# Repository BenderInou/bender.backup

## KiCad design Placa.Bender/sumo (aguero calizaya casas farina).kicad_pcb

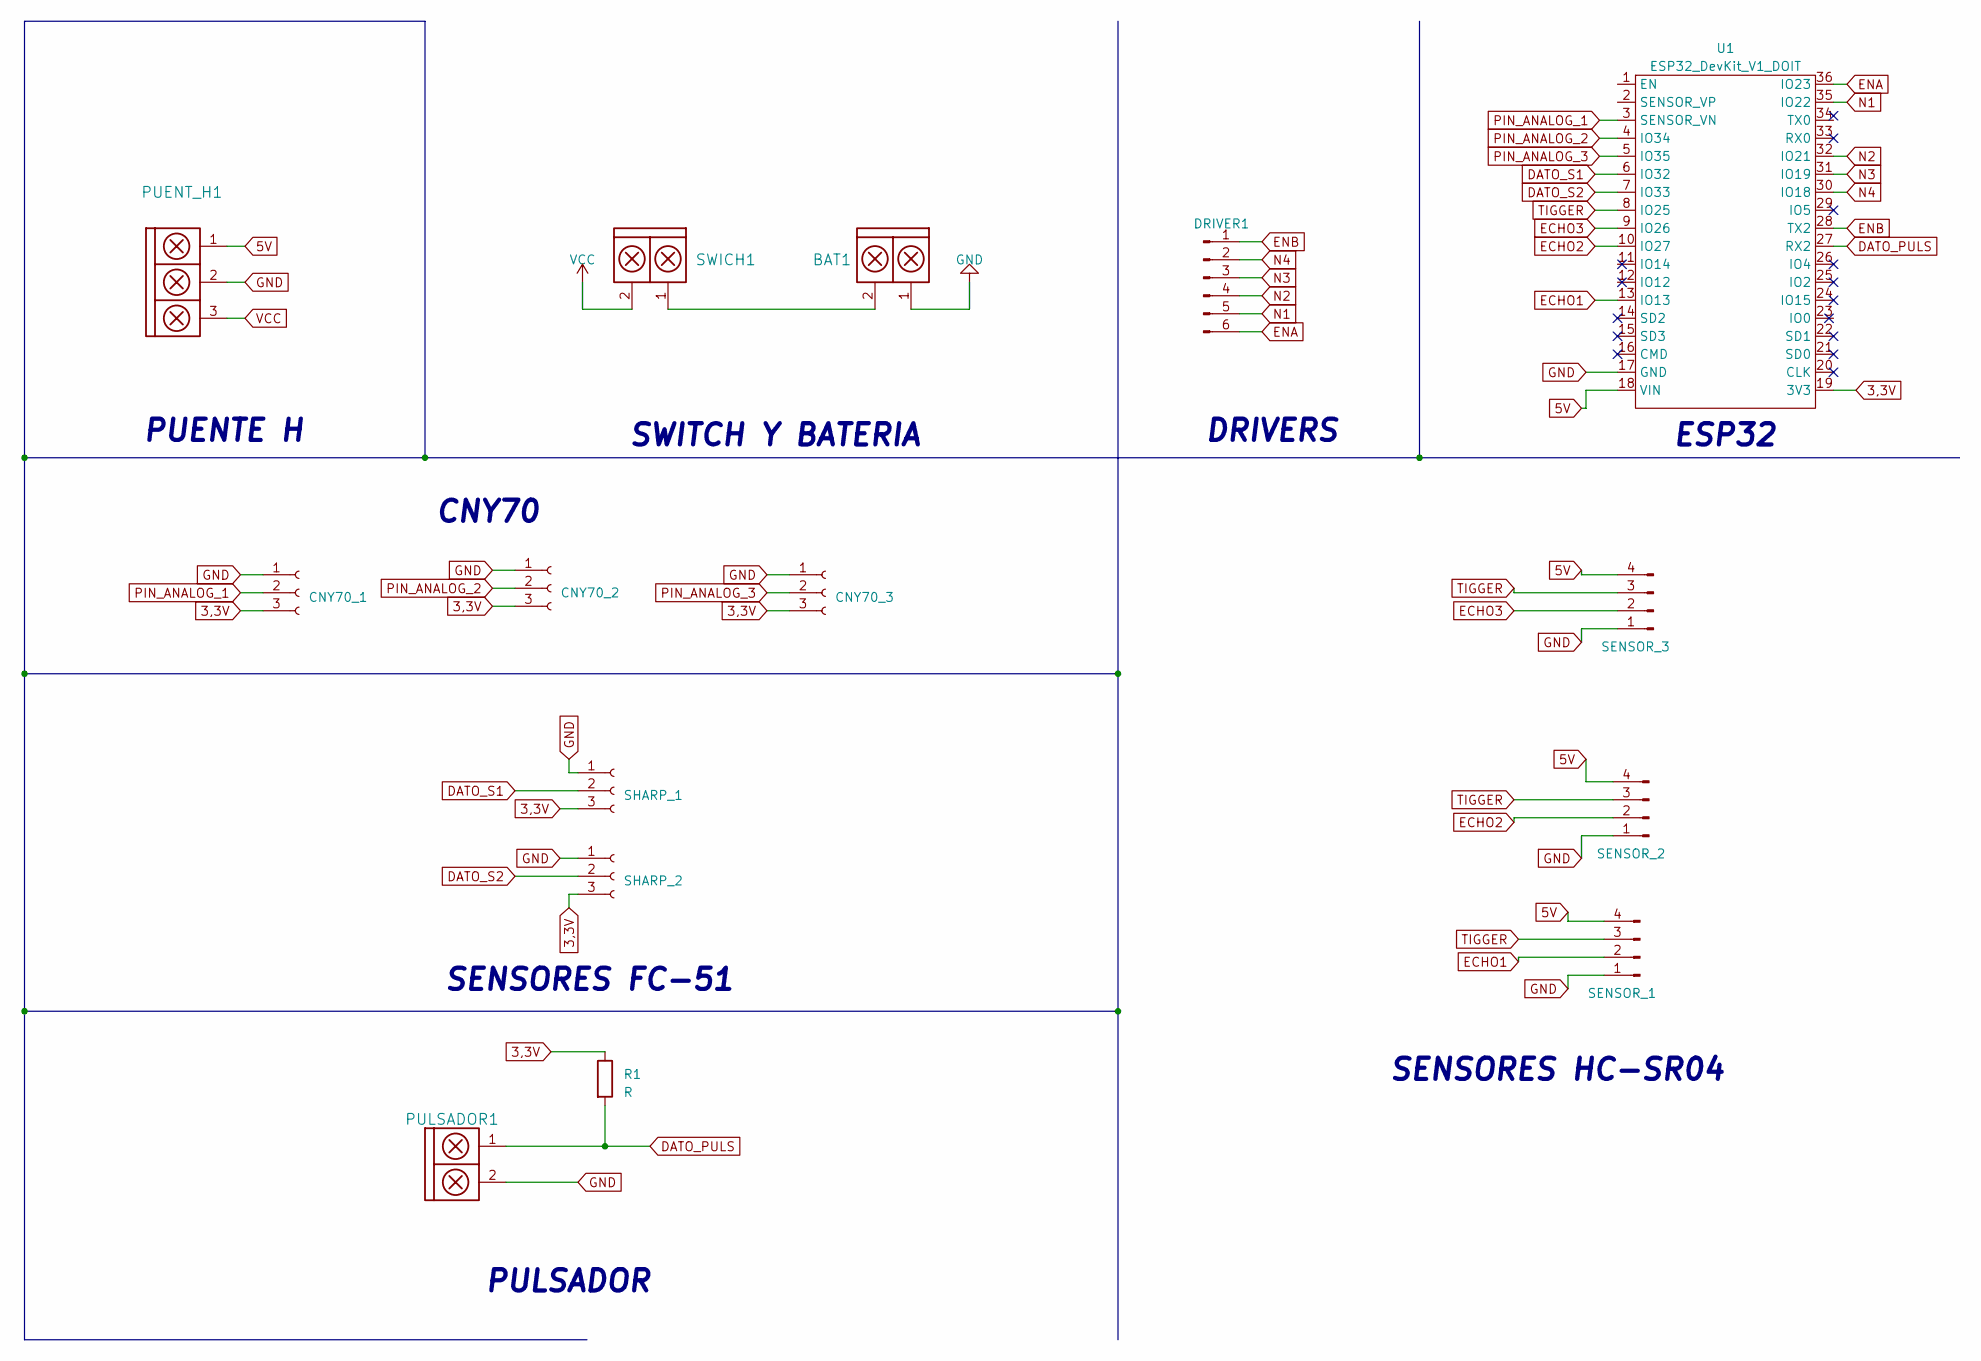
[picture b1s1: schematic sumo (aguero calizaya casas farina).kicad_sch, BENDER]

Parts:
BAT1: BORNERA2
CNY70_1, CNY70_2, CNY70_3: Pin_Header_3
DRIVER1: Pin_Header_6
PUENT_H1: \; BORNERA3
PULSADOR1: BORNERA2
R1: R; RES0.2
SENSOR_1, SENSOR_2, SENSOR_3: Pin_Header_Angled_1x04
SHARP_1, SHARP_2: Pin_Header_3
SWICH1: BORNERA2
U1: ESP32_DevKit_V1_DOIT; ESP32_DEVKIT_V1_DOIT

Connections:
3,3V: CNY70_1.3, CNY70_2.3, CNY70_3.3, R1.1, SHARP_1.3, SHARP_2.3, U1.19 (3V3)
5V: PUENT_H1.1, SENSOR_1.4, SENSOR_2.4, SENSOR_3.4, U1.18 (VIN)
DATO_PULS: PULSADOR1.1, R1.2, U1.27 (RX2)
DATO_S1: SHARP_1.2, U1.6 (IO32)
DATO_S2: SHARP_2.2, U1.7 (IO33)
ECHO1: SENSOR_1.2, U1.13 (IO13)
ECHO2: SENSOR_2.2, U1.10 (IO27)
ECHO3: SENSOR_3.2, U1.9 (IO26)
ENA: DRIVER1.6, U1.36 (IO23)
ENB: DRIVER1.1, U1.28 (TX2)
GND: BAT1.1, CNY70_1.1, CNY70_2.1, CNY70_3.1, PUENT_H1.2, PULSADOR1.2, SENSOR_1.1, SENSOR_2.1, SENSOR_3.1, SHARP_1.1, SHARP_2.1, U1.17 (GND)
N1: DRIVER1.5, U1.35 (IO22)
N2: DRIVER1.4, U1.32 (IO21)
N3: DRIVER1.3, U1.31 (IO19)
N4: DRIVER1.2, U1.30 (IO18)
unnamed: BAT1.2, SWICH1.1
PIN_ANALOG_1: CNY70_1.2, U1.3 (SENSOR_VN)
PIN_ANALOG_2: CNY70_2.2, U1.4 (IO34)
PIN_ANALOG_3: CNY70_3.2, U1.5 (IO35)
TIGGER: SENSOR_1.3, SENSOR_2.3, SENSOR_3.3, U1.8 (IO25)
VCC: PUENT_H1.3, SWICH1.2

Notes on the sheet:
SENSORES FC-51
PUENTE H
PULSADOR
CNY70
DRIVERS
SWITCH Y BATERIA
SENSORES HC-SR04
ESP32

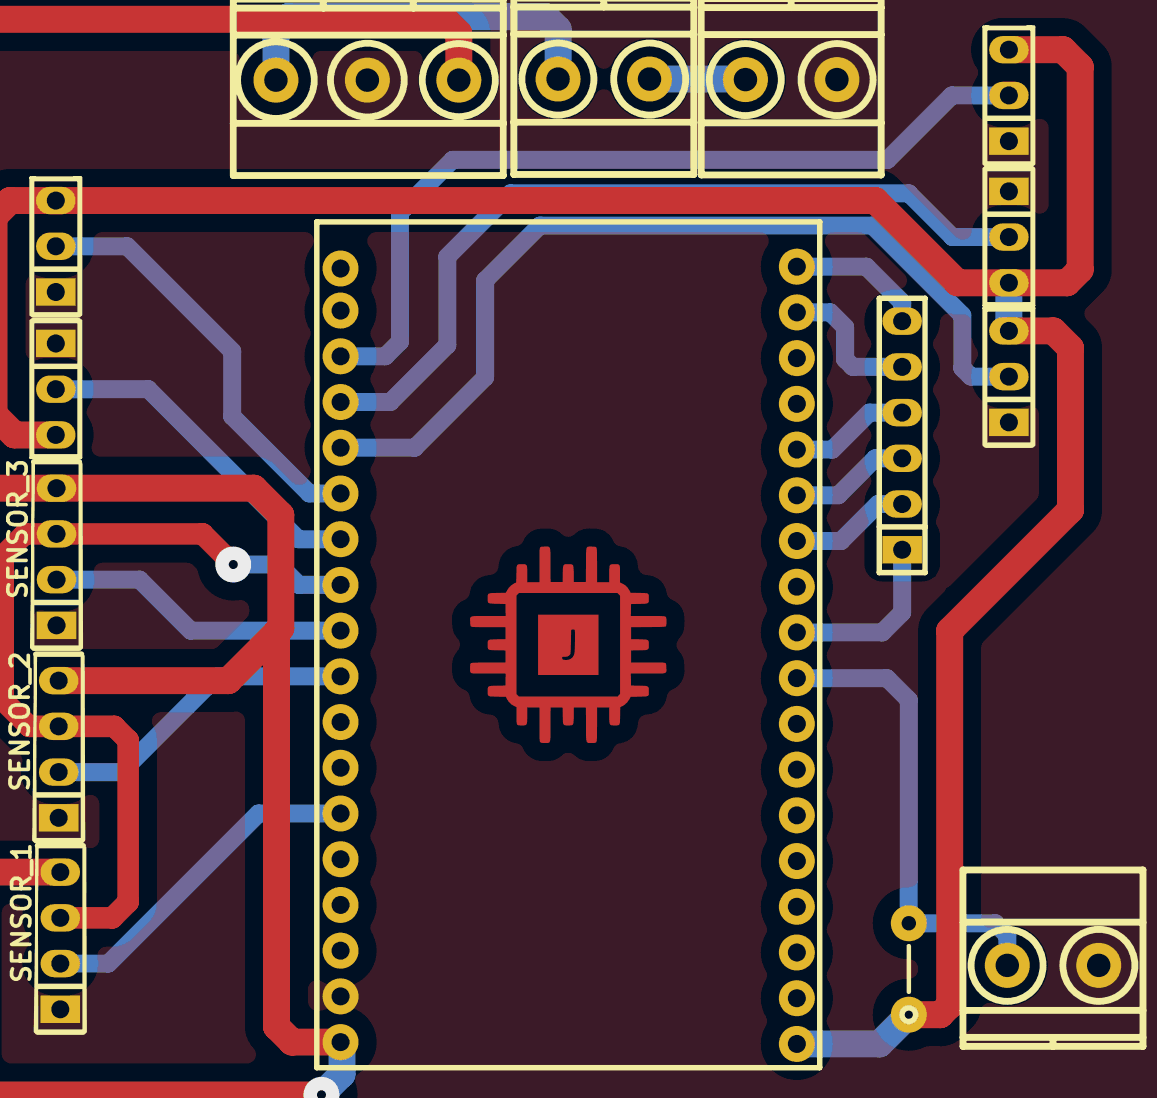
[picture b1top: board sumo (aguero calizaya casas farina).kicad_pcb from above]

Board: 2 copper layers, 15 parts (0 on the bottom side), 21 nets.

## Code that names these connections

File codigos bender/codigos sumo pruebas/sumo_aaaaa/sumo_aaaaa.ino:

//    ___________________ UN SOLO TRIGGER ____________

// Definimos los pines a utilizar
const int Trigger = 25;
const int Echo1 = 13;
const int Echo2 = 27;
const int Echo3 = 26;
const int LedPin = 2;

// Función para obtener la distancia en cm
float getDistance(int triggerPin, int echoPin) {
  digitalWrite(triggerPin, LOW);
  delayMicroseconds(2);
  digitalWrite(triggerPin, HIGH);
  delayMicroseconds(10);
  digitalWrite(triggerPin, LOW);
  long duration = pulseIn(echoPin, HIGH);
  float distance = duration / 59.0;
  return distance;
}

// Función para actualizar los valores de las distancias y mostrarlos por Serial
void updateAndPrintDistances() {
  float distance1 = getDistance(Trigger, Echo1);
  float distance2 = getDistance(Trigger, Echo2);
  float distance3 = getDistance(Trigger, Echo3);
  Serial.print("Distancia 1: ");
  Serial.print(distance1);
  Serial.print(" cm, Distancia 2: ");
  Serial.print(distance2);
  Serial.print(" cm, Distancia 3: ");
  Serial.print(distance3);
  Serial.println(" cm");
}

// Función para encender o apagar un LED según la distancia
void controlLed(float distance) {
  if (distance <= 10) {
    digitalWrite(LedPin, HIGH);
  } else {
    digitalWrite(LedPin, LOW);
  }
}

void setup() {
  Serial.begin(9600);
  pinMode(Trigger, OUTPUT);
  pinMode(Echo1, INPUT);
  pinMode(Echo2, INPUT);
  pinMode(Echo3, INPUT);
  pinMode(LedPin, OUTPUT);
}

void loop() {
  updateAndPrintDistances();
  float distance1 = getDistance(Trigger, Echo1);
  float distance2 = getDistance(Trigger, Echo2);
  float distance3 = getDistance(Trigger, Echo3);
  controlLed(distance1);
   delayMicroseconds(10);
}

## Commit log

2023-07-12 benderbakup
2023-07-12 test
2023-07-12 actualizacion
2023-07-12 Create codigos del sumo bender
2023-07-12 eliminacion de coso
2023-11-24 2.056
